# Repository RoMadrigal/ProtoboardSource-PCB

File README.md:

# ProtoboardSource-PCB
Repositorio del diseño de una PCB que permite conectar directamente cables con conector banana para alimentar una protoboard

Este repositorio y sus contenidos fueron diseñados por:

<div align="center">

|        **Nombre**      | **Correo electrónico**|
|:---------------------------:|:---------------------:|
|   Rodrigo Madrigal Montes   |  rmadrigalmontes@gmail.com |

</div>

## Agradecimientos a PCBWay

Quiero expresar mi agradecimiento a **PCBWay** por su colaboración y apoyo en la fabricación de esta PCB. La calidad de las placas recibidas, tanto en precisión de fabricación como en acabados, encajaron perfectamente con las dimensiones y especificaciones con las que las diseñé. Esto siempre es vital y más aún en una PCB de este tipo que debe encajar en una *Protoboard* con dimensiones muy específicas. 

### PCB ensamblada

Una vez recibidas las placas de **PCBWay**, se procedió con el ensamblaje manual de todos los componentes. A continuación se muestran imágenes del resultado final:

<div align="center">

|  |
|:--:|
| *PCB ensamblada - no montada en la Protoboard* |

</div>

<div align="center">

|  |
|:--:|
| *PCB ensamblada - montada en la Protoboard* |

</div>

### Demostración de funcionamiento

A continuación, se presentan imágenes mostrando la PCB montada en una *Protoboard* y conectada a una fuente de tensión de laboratorio, y midiendo la tensión que suministra con un multímetro:

<div align="center">

|  |
|:--:|
| *Fuente de laboratorio ajustada en 3.68 V* |

</div>

<div align="center">

|  |
|:--:|
| *PCB conectada a la fuente y montada en la Protoboard* |

</div>

<div align="center">

|  |
|:--:|
| *Medida de tensión suministrada a la Protoboard* |

</div>

Gracias a su servicio confiable y de altísima calidad, logré ensamblar y probar con éxito esta PCB, cumpliendo el objetivo del diseño. Recomiendo sus servicios para estudiantes, profesionales y cualquier persona interesada en manufacturar PCBs de alta calidad. Más información en [pcbway.com](https://www.pcbway.com).

## Organización y contenido de los directorios 

Este repositorio contiene dos directorios principales, cuyos contenidos son:

- `kicad_project`: Contiene los archivos de diseño y configuarción del proyecto
    - `CargadorWalkieTalkie.kicad_pcb`
    - `CargadorWalkieTalkie.kicad_pro`
    - `CargadorWalkieTalkie.kicad_sch`

- `outputs`: Contiene todos los archivos de salida de *KiCad*

Si se desea utilizar este diseño y manufacturarlo por medio de un fabricante se debe comprimir los archivos incluidos en la carpeta `outputs` en un archivo `.zip` y este se puede cargar en la página del fabricante para ordenar la fabricación de la PCB. 

## Diseño del esquemático

El propósito del circuito es poder alimentar de forma segura y firme una *protoboard* o *breadboard* con cables banana provenientes de fuentes profesionales de laboratorio, para evitar conexiones flojas, peligrosas e ineficientes; como por ejemplo enrollar un cable alrededor del conector banana e introducirlo luego en la *protoboard*. 

Para solucionar este problema se propone el circuito representado en el siguiente esquemático:

<div align="center">

|  |
|:--:|
| *Diseño del esquemático* |

</div>

Como se observa se cuenta con dos circuitos de alimentación idénticos por separado, uno para cada pista de alimentación de la protoboard. Además en cada circuito se encuentra un capacitor que tiene la función de filtrar ruido proveniente de la fuente de alimentación que se esté utilizando. 

Otra observación importante es el hecho de que los conectores que entran en lo pines de la *protoboard* están conectados en paralelo, se tomó la decisión de usar cinco pares de pines entre el positivo y negativo de la fuente en lugar de un solo par de pines para dar mayor estabilidad al momento de conectarse en la *protoboard*. Pero si se desea usar menos pines al estar todos en paralelo no habría ningún problema si se decide hacerlo de esta manera. 

## Lista de componentes

A continuación se incluye una lista con los componentes utilizados en el diseño, con el mismo número que se les asignó en el diseño final de PCB:

<div align="center">

|   Componente   |   Valor / Modelo    |    Descripción    |
|:--------------:|:-------------------:|:-----------------:|
| C1 / C2   |   10 µF a 50 V           |   Capacitor cerámico SMD 1206    |
| Pines para conectar a la Protoboard    |     Pin Headers de 2.54mm de separación y 11.5mm de longitud   |   Pin Headers     |
|Conectores Banana para alimentación    |     Conector Banana Hembra para chasis           |   Conector Banana Hembra     |
| Postes de nylon    |     Postes y tuercas de nylon M3           |   Postes y tuercas de nylon     |

</div>

## Diseño de la PCB

Una vez definido el circuito final, se diseñó la PCB en *KiCad* con una arquitectura de **dos capas**:

- **F.Cu**: Plano de alimentación (VCC y VDD)
- **B.Cu**: Plano de tierra (GND1 y GND2)

### Capas de la PCB

<div align="center">

|  |
|:-----------------------------:|
|    *Capa superior (F.Cu)*     |

</div>

<div align="center">

|  |
|:-----------------------------:|
|    *Capa inferior (B.Cu)*     |

</div>

> [!NOTE]
> Se observa como los planos de alimentación positiva (VCC, VDD) y alimentación negativa (GND1, GND2) están separados por un espaciado físico en la parte central de la PCB para evitar cualquier tipo de interferencia o fuga de corriente entre ambos rieles de alimentación al conectarlo en la *Protoboard*.

Además, se agregaron zonas de serigrafía, agujeros de montaje, así como textos identificativos y un logotipo en el *silkscreen*, además del nombre del proyecto y los datos del autor. Finalmente se muestran resultados de la vista 3D de la PCB en KiCad. 

<div align="center">

|  |
|:--:|
| *Vista 3D Frontal de la PCB en KiCad* |

</div>

<div align="center">

|  |
|:--:|
| *Vista 3D Trasera de la PCB en KiCad* |

</div>

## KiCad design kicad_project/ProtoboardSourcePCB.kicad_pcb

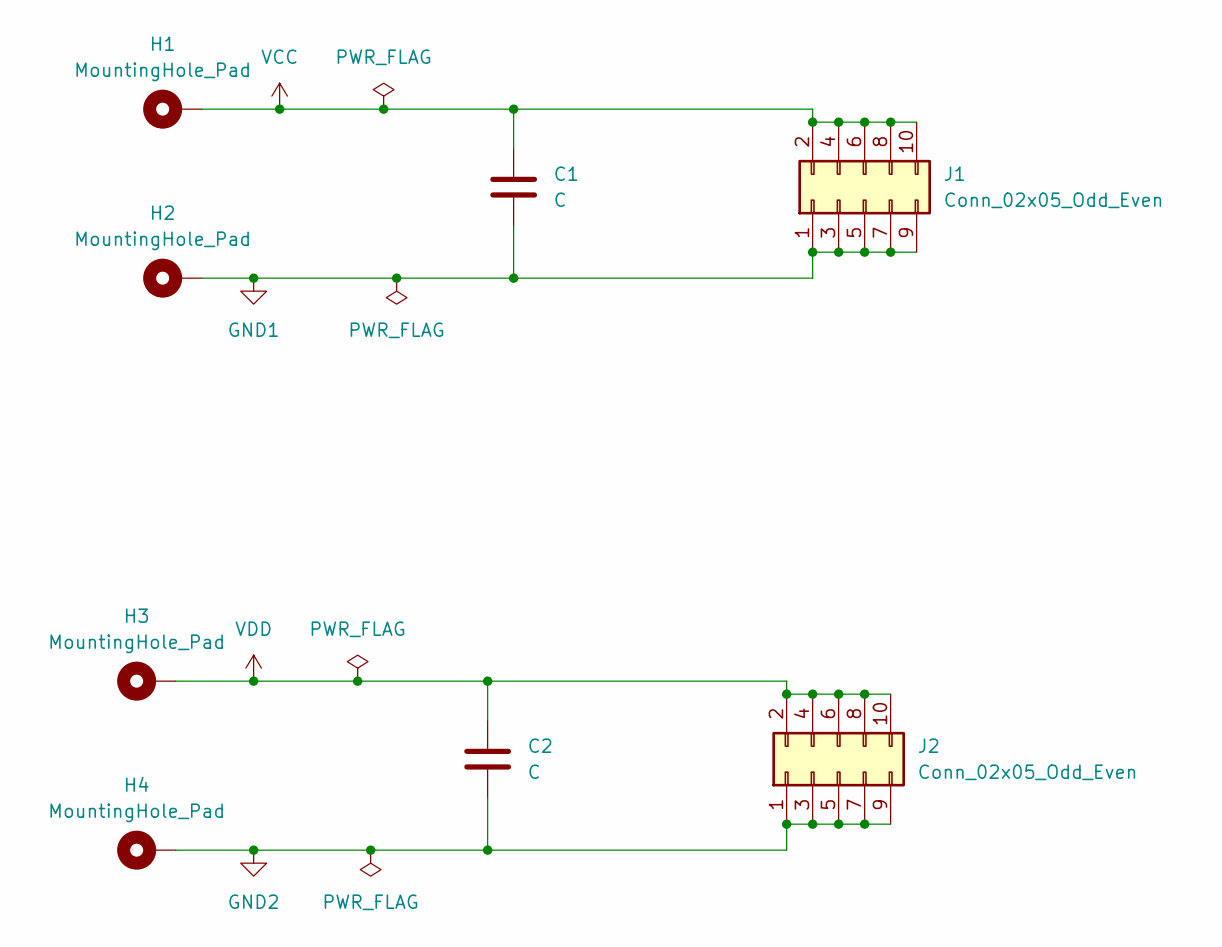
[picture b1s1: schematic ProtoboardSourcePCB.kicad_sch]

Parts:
C1, C2: C; C_1206_3216Metric_Pad1.33x1.80mm_HandSolder
H1, H2, H3, H4: MountingHole_Pad; MountingHole_6mm_Pad
J1, J2: Conn_02x05_Odd_Even; PinHeader_2x05_P2.54mm_Vertical

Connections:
GND1: C1.2, H2.1, J1.1, J1.3, J1.5, J1.7, J1.9
GND2: C2.2, H4.1, J2.1, J2.3, J2.5, J2.7, J2.9
VCC: C1.1, H1.1, J1.2, J1.4, J1.6, J1.8, J1.10
VDD: C2.1, H3.1, J2.2, J2.4, J2.6, J2.8, J2.10

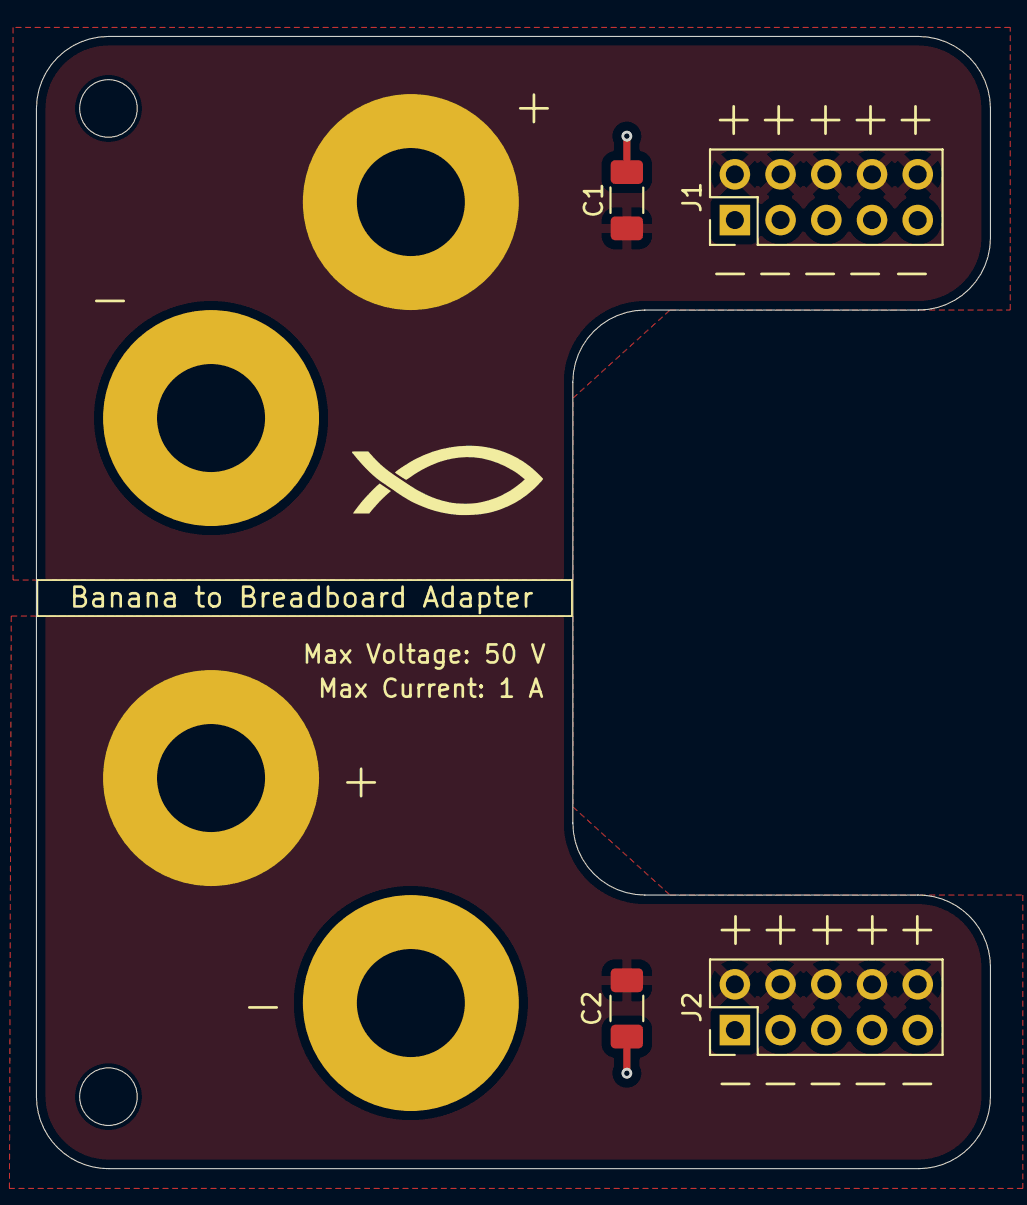
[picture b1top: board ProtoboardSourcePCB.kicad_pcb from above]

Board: 2 copper layers, 53.0 x 62.9 mm, 8 parts (0 on the bottom side), 4 nets.

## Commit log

2025-07-23 Agregando archivos del proyecto de KiCad
2025-07-23 Agregando nombre del autor en el README.md
2025-07-24 Corrigiendo huellas, colocando componentes y delimitando espacio de la PCB
2025-07-27 Modificando huella de los capacitores y reacomodando componentes
2025-07-27 Modificando dimensiones de la PCB y agregando texto en Silkscreen
2025-07-29 Agregando agujeros de montaje en la PCB
2025-07-29 Definiendo los planos de tierra y alimentacion, y agregando vias para los capacitores
2025-08-07 Modificando huellas de conector banana y reacomodando huella de C2
2025-08-08 Se agregan imagenes en la carpeta images y se agregan secciones en el README.md
2025-08-08 Agregando especificaciones y nombres en la Silkscreen de la PCB
2025-08-15 Agregando ultimos detalles y logo en el Silkscreen
2025-09-12 Agregando archivos de fabricacion en el directorio outputs
2025-09-12 Se agregan logo y ultima reubicacion de componentes en la PCB
2025-09-12 Agregando demostracion de funcionamiento y agradecimentos a PCBWay en el README.md
2025-10-07 Agregando directorio de modelos 3D en la carpeta del proyecto
2025-10-07 Modificando imagenes de vista 3D con modelos 3D agregados en el README.md
